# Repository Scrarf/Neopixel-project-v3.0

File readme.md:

# (work in progress) Status: Hardware verification. 

# Introduction:
A dimmable RGBW LED controller that can be controlled with wifi or bluetooth. A constant current DC-DC buck converter provides stable current to all leds connected in series, up to 3A. Currently, it is programmed for 300mah by R22 current sensing resistor for the apropriate onboard 300mah LEDs.

# 3D render:

# Schematic:

# Layout:

# Bill of materials:

|Reference               |Value               |Datasheet                                                                                           |Footprint                                                                         |Qty|PPU   |DNP|
|------------------------|--------------------|----------------------------------------------------------------------------------------------------|----------------------------------------------------------------------------------|---|------|---|
|C1,C2,C14               |100µF               |https://www.lcsc.com/datasheet/C22383783.pdf                                                        |Capacitor_SMD:CP_Elec_6.3x7.7                                                     |3  |0.0193|   |
|C3,C15,C16              |22µF                |https://www.lcsc.com/datasheet/C22367832.pdf                                                        |Capacitor_SMD:C_0805_2012Metric                                                   |3  |0.1158|   |
|C4                      |1µF                 |https://www.lcsc.com/datasheet/C15849.pdf                                                           |Capacitor_SMD:C_0603_1608Metric                                                   |1  |0.0038|   |
|C5                      |10nF                |https://www.lcsc.com/datasheet/C60133.pdf                                                           |Capacitor_SMD:C_0402_1005Metric                                                   |1  |0.0009|   |
|C6,C7,C9,C10,C11,C12,C13|100nF               |https://www.lcsc.com/datasheet/C14663.pdf                                                           |Capacitor_SMD:C_0603_1608Metric                                                   |7  |0.0021|   |
|C8                      |10µF                |https://www.lcsc.com/datasheet/C33546007.pdf                                                        |Capacitor_SMD:C_0805_2012Metric                                                   |1  |0.0178|   |
|C17,C18                 |24pF                |https://www.lcsc.com/datasheet/C541435.pdf                                                          |Capacitor_SMD:C_0402_1005Metric                                                   |2  |0.0033|   |
|C19,C20                 |DNP                 |~                                                                                                   |Capacitor_SMD:C_0402_1005Metric                                                   |2  |0     |DNP|
|D1                      |W                   |https://www.lcsc.com/datasheet/C7500126.pdf                                                         |LED_SMD:LED_PLCC_2835                                                             |1  |0.069 |   |
|D2                      |R                   |https://www.lcsc.com/datasheet/C1322327.pdf                                                         |LED_SMD:LED_Luminus_MP-3030-1100_3.0x3.0mm                                        |1  |0.1638|   |
|D3                      |G                   |https://www.lcsc.com/datasheet/C1322328.pdf                                                         |LED_SMD:LED_Luminus_MP-3030-1100_3.0x3.0mm                                        |1  |0.1589|   |
|D4                      |B                   |https://www.lcsc.com/datasheet/C1322329.pdf                                                         |LED_SMD:LED_Luminus_MP-3030-1100_3.0x3.0mm                                        |1  |0.0962|   |
|D5                      |SS34                |https://www.lcsc.com/datasheet/C8678.pdf                                                            |Diode_SMD:D_SMA                                                                   |1  |0.0265|   |
|HS1                     |Heatsink            |https://www.lcsc.com/datasheet/C286191.pdf                                                          |22x22x10                                                                          |1  |0.1324|   |
|J1                      |Conn_01x03_Pin      |https://www.lcsc.com/datasheet/C5383112.pdf                                                         |Connector_PinHeader_2.54mm:PinHeader_1x03_P2.54mm_Vertical                        |1  |0.0105|   |
|J3                      |Screw_Terminal_01x02|https://www.lcsc.com/datasheet/C5188442.pdf                                                         |TerminalBlock_Phoenix:TerminalBlock_Phoenix_MPT-0,5-2-2.54_1x02_P2.54mm_Horizontal|1  |0.1513|   |
|L1                      |68µH                |https://www.lcsc.com/datasheet/C2929435.pdf                                                         |Inductor_SMD:L_Ferrocore_DLG-0504                                                 |1  |0.052 |   |
|L2                      |2nH                 |https://www.lcsc.com/datasheet/C395081.pdf                                                          |Inductor_SMD:L_0603_1608Metric                                                    |1  |0.0069|   |
|L3                      |22µH                |https://www.lcsc.com/datasheet/C41408473.pdf                                                        |Inductor_SMD:L_Ferrocore_DLG-0302                                                 |1  |0.0184|   |
|L4                      |24nH                |https://www.lcsc.com/datasheet/C139271.pdf                                                          |Inductor_SMD:L_0603_1608Metric                                                    |1  |0.0064|   |
|L5                      |0                   |https://www.lcsc.com/datasheet/C106231.pdf                                                          |Inductor_SMD:L_0402_1005Metric                                                    |1  |0.0006|   |
|Q1,Q2,Q3,Q4             |MMBT3904            |https://www.lcsc.com/datasheet/C2762221.pdf                                                         |Package_TO_SOT_SMD:SOT-23                                                         |4  |0.0095|   |
|Q5,Q6,Q7,Q8             |DO3407B             |https://www.lcsc.com/datasheet/C41367402.pdf                                                        |Package_TO_SOT_SMD:SOT-23-3                                                       |4  |0.0271|   |
|R1,R3,R5,R7             |1k5                 |https://www.lcsc.com/datasheet/C2980089.pdf                                                         |Resistor_SMD:R_1206_3216Metric                                                    |4  |0.013 |   |
|R2,R4,R6,R8             |200                 |https://www.lcsc.com/datasheet/C3014166.pdf                                                         |Resistor_SMD:R_0805_2012Metric                                                    |4  |0.0156|   |
|R9,R10,R11,R12,R17      |5k1                 |https://www.lcsc.com/datasheet/C103696.pdf                                                          |Resistor_SMD:R_0603_1608Metric                                                    |5  |0.0009|   |
|R15                     |1M                  |https://www.lcsc.com/datasheet/C103216.pdf                                                          |Resistor_SMD:R_0603_1608Metric                                                    |1  |0.001 |   |
|R16                     |16k                 |https://www.lcsc.com/datasheet/C137788.pdf                                                          |Resistor_SMD:R_0603_1608Metric                                                    |1  |0.0012|   |
|R22                     |0.333               |https://www.lcsc.com/datasheet/C160932.pdf                                                          |Resistor_SMD:R_2512_6332Metric                                                    |1  |0.0488|   |
|SW1,SW2                 |TS-1088-AR02016     |https://www.lcsc.com/datasheet/C720477.pdf                                                          |TS-1088-AR02016:SW_TS-1088_XNP                                                    |2  |0.0415|   |
|U1                      |ESP8685H4           |https://www.lcsc.com/datasheet/C4944062.pdf                                                         |ESP8685:QFN284X4_EXP                                                              |1  |1.3435|   |
|U2                      |AL8843              |https://www.lcsc.com/datasheet/lcsc_datasheet_2412251103_Diodes-Incorporated-AL8843SP-13_C507866.pdf|Package_SO:Diodes_SO-8EP                                                          |1  |0.3568|   |
|U3                      |TD1469              |https://www.lcsc.com/datasheet/C2832208.pdf                                                         |Package_TO_SOT_SMD:TSOT-23-6                                                      |1  |0.2999|   |
|U4                      |USBLC6-4SC6         |https://www.lcsc.com/datasheet/C19170931.pdf                                                        |Package_TO_SOT_SMD:SOT-23-6                                                       |1  |0.0273|   |
|Y1                      |Crystal_GND24       |https://www.lcsc.com/datasheet/C501793.pdf                                                          |Crystal:Crystal_SMD_Abracon_ABM8AIG-4Pin_3.2x2.5mm                                |1  |0.0922|   |

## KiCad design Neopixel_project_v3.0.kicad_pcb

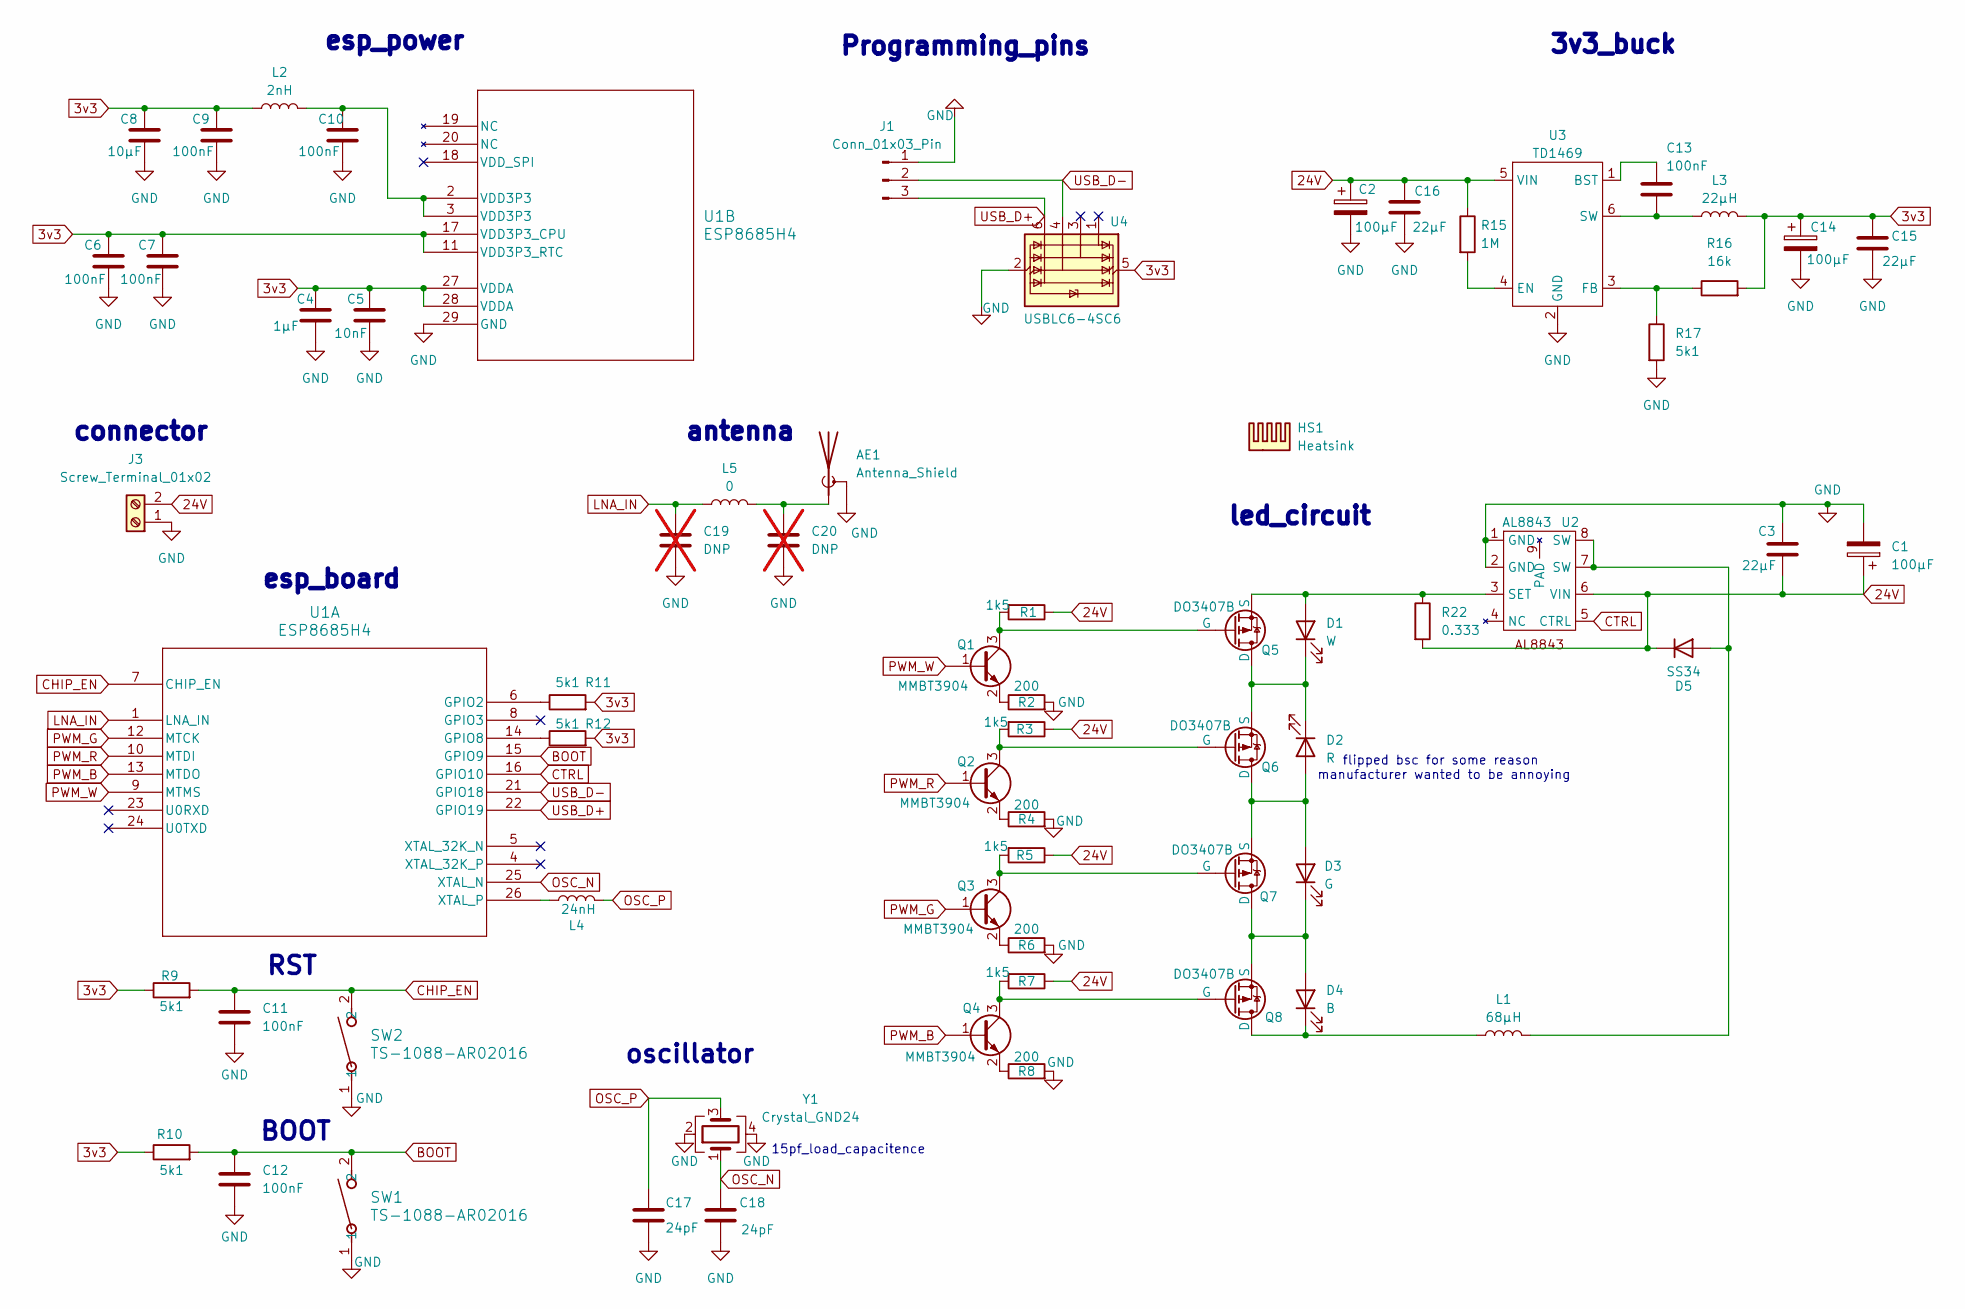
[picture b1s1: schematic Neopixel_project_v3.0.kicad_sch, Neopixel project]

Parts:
AE1: Antenna_Shield; Texas_SWRA117D_2.4GHz_Left
C1, C2, C14: 100µF; CP_Elec_6.3x7.7
C3, C15, C16: 22µF; C_0805_2012Metric
C4: 1µF; C_0603_1608Metric
C5: 10nF; C_0402_1005Metric
C6, C7, C9, C10, C11, C12, C13: 100nF; C_0603_1608Metric
C8: 10µF; C_0805_2012Metric
C17, C18: 24pF; C_0402_1005Metric
C19, C20: DNP; C_0402_1005Metric; not fitted
D1: W; LED_PLCC_2835
D2: R; LED_Luminus_MP-3030-1100_3.0x3.0mm
D3: G; LED_Luminus_MP-3030-1100_3.0x3.0mm
D4: B; LED_Luminus_MP-3030-1100_3.0x3.0mm
D5: SS34; D_SMA
HS1: Heatsink; 22x22x10
J1: Conn_01x03_Pin; PinHeader_1x03_P2.54mm_Vertical
J3: Screw_Terminal_01x02; TerminalBlock_Phoenix_MPT-0,5-2-2.54_1x02_P2.54mm_Horizontal
L1: 68µH; L_Ferrocore_DLG-0504
L2: 2nH; L_0603_1608Metric
L3: 22µH; L_Ferrocore_DLG-0302
L4: 24nH; L_0603_1608Metric
L5: 0; L_0402_1005Metric
Q1, Q2, Q3, Q4: MMBT3904; SOT-23
Q5, Q6, Q7, Q8: DO3407B; SOT-23-3
R1, R3, R5, R7: 1k5; R_1206_3216Metric
R2, R4, R6, R8: 200; R_0805_2012Metric
R9, R10, R11, R12, R17: 5k1; R_0603_1608Metric
R15: 1M; R_0603_1608Metric
R16: 16k; R_0603_1608Metric
R22: 0.333; R_2512_6332Metric
SW1, SW2: TS-1088-AR02016; SW_TS-1088_XNP
U1: ESP8685H4; QFN284X4_EXP
U2: AL8843; Diodes_SO-8EP
U3: TD1469; TSOT-23-6
U4: USBLC6-4SC6; SOT-23-6
Y1: Crystal_GND24; Crystal_SMD_Abracon_ABM8AIG-4Pin_3.2x2.5mm

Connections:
3v3: C4.1, C5.1, C6.1, C7.1, C8.1, C9.1, C14.1, C15.1, L2.1, L3.2, R9.1, R10.1, R11.2, R12.2, R16.2, U1.11 (VDD3P3_RTC), U1.17 (VDD3P3_CPU), U1.27 (VDDA), U1.28 (VDDA), U4.5 (VBUS)
24V: C1.1, C2.1, C3.2, C16.1, D5.1 (K), J3.2, R1.1, R3.1, R5.1, R7.1, R15.1, R22.2, U2.6 (VIN), U3.5 (VIN)
BOOT: C12.1, R10.2, SW1.2, U1.15 (GPIO9)
CHIP_EN: C11.1, R9.2, SW2.2, U1.7 (CHIP_EN)
CTRL: U1.16 (GPIO10), U2.5 (CTRL)
GND: AE1.2 (Shield), C1.2, C2.2, C3.1, C4.2, C5.2, C6.2, C7.2, C8.2, C9.2, C10.2, C11.2, C12.2, C14.2, C15.2, C16.2, C17.2, C18.2, C19.2, C20.2, J1.1, J3.1, R2.2, R4.2, R6.2, R8.2, R17.2, SW1.1, SW2.1, U1.29 (GND), U2.1 (GND), U2.2 (GND), U3.2 (GND), U4.2 (GND), Y1.2, Y1.4
LNA_IN: C19.1, L5.1, U1.1 (LNA_IN)
unnamed: AE1.1 (A), C20.1, L5.2
unnamed: C10.1, L2.2, U1.2 (VDD3P3), U1.3 (VDD3P3)
unnamed: D1.2 (A), Q5.3 (S), R22.1, U2.3 (SET)
unnamed: D1.1 (K), D2.1 (K), Q5.1 (D), Q6.3 (S)
unnamed: D2.2 (A), D3.2 (A), Q6.1 (D), Q7.3 (S)
unnamed: D3.1 (K), D4.2 (A), Q7.1 (D), Q8.3 (S)
unnamed: D4.1 (K), L1.1, Q8.1 (D)
unnamed: D5.2 (A), L1.2, U2.7 (SW), U2.8 (SW)
unnamed: Q1.3 (C), Q5.2 (G), R1.2
unnamed: Q1.2 (E), R2.1
unnamed: Q2.3 (C), Q6.2 (G), R3.2
unnamed: Q2.2 (E), R4.1
unnamed: Q3.3 (C), Q7.2 (G), R5.2
unnamed: Q3.2 (E), R6.1
unnamed: Q4.3 (C), Q8.2 (G), R7.2
unnamed: Q4.2 (E), R8.1
unnamed: R11.1, U1.6 (GPIO2)
unnamed: R12.1, U1.14 (GPIO8)
unnamed: L4.1, U1.26 (XTAL_P)
unnamed: C13.1, U3.1 (BST)
unnamed: R15.2, U3.4 (EN)
unnamed: R16.1, R17.1, U3.3 (FB)
unnamed: C13.2, L3.1, U3.6 (SW)
OSC_N: C18.1, U1.25 (XTAL_N), Y1.1
OSC_P: C17.1, L4.2, Y1.3
PWM_B: Q4.1 (B), U1.13 (MTDO)
PWM_G: Q3.1 (B), U1.12 (MTCK)
PWM_R: Q2.1 (B), U1.10 (MTDI)
PWM_W: Q1.1 (B), U1.9 (MTMS)
USB_D+: J1.3, U1.22 (GPIO19), U4.6 (I/O4)
USB_D-: J1.2, U1.21 (GPIO18), U4.4 (I/O3)

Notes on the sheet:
RST
esp_power
led_circuit
flipped bsc for some reason manufacturer wanted to be annoying
connector
3v3_buck
antenna
Programming_pins
15pf_load_capacitence
oscillator
BOOT
esp_board

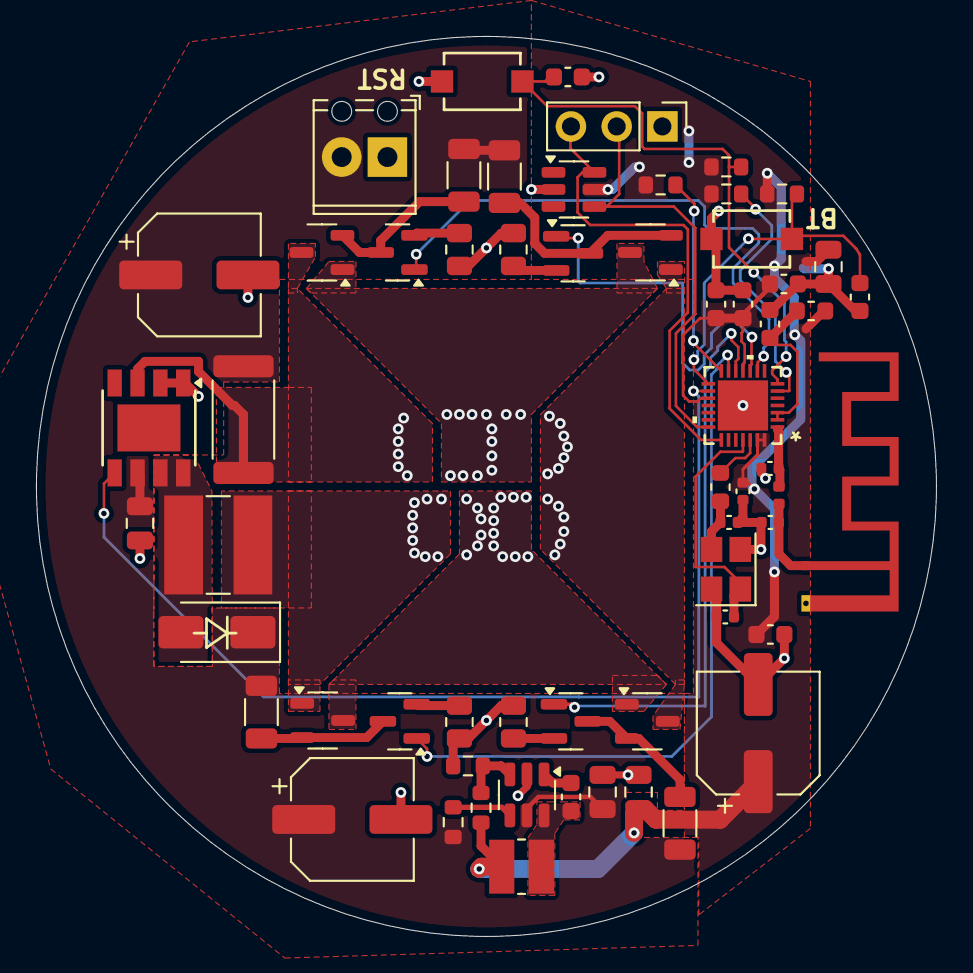
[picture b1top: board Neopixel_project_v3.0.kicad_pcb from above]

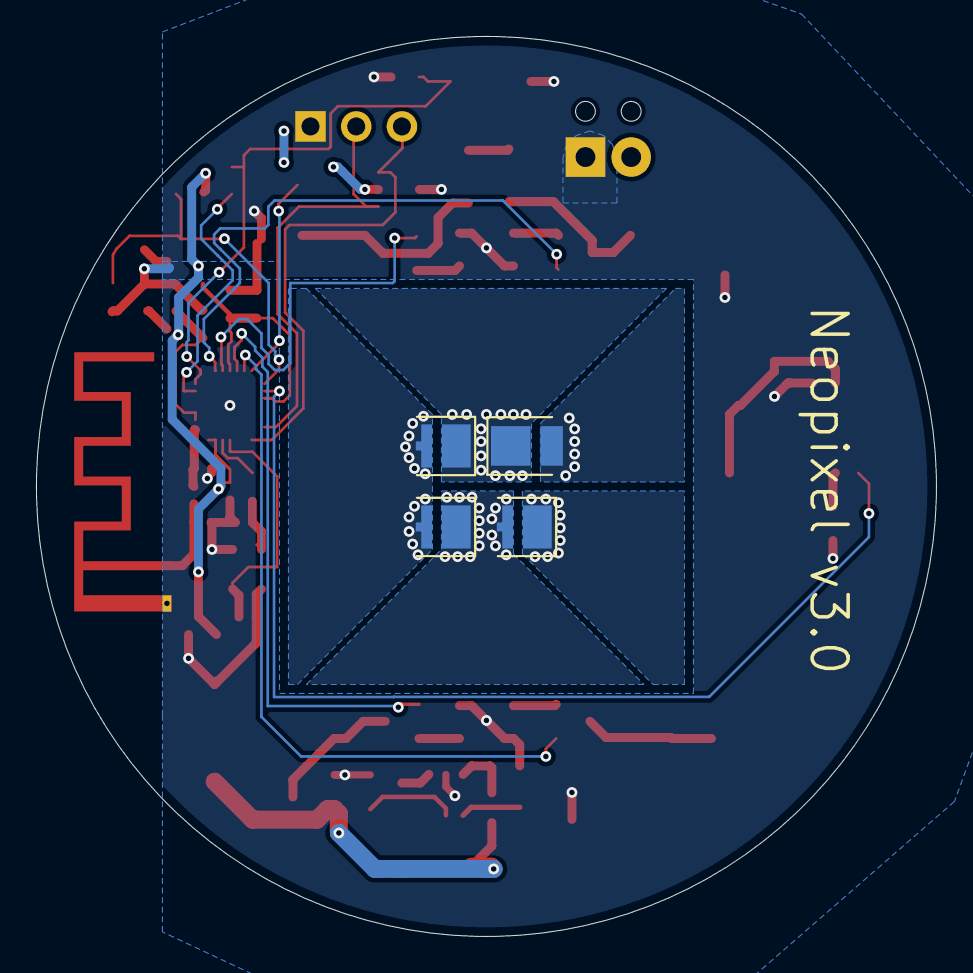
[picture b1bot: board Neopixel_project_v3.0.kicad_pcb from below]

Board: 2 copper layers, 50.0 x 50.0 mm, 64 parts (4 on the bottom side), 38 nets.

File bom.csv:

"Reference","Value","Datasheet","Footprint","Qty","PPU","DNP"
"C1,C2,C14","100µF","https://www.lcsc.com/datasheet/C22383783.pdf","Capacitor_SMD:CP_Elec_6.3x7.7","3","0.0193",""
"C3,C15,C16","22µF","https://www.lcsc.com/datasheet/C22367832.pdf","Capacitor_SMD:C_0805_2012Metric","3","0.1158",""
"C4","1µF","https://www.lcsc.com/datasheet/C15849.pdf","Capacitor_SMD:C_0603_1608Metric","1","0.0038",""
"C5","10nF","https://www.lcsc.com/datasheet/C60133.pdf","Capacitor_SMD:C_0402_1005Metric","1","0.0009",""
"C6,C7,C9,C10,C11,C12,C13","100nF","https://www.lcsc.com/datasheet/C14663.pdf","Capacitor_SMD:C_0603_1608Metric","7","0.0021",""
"C8","10µF","https://www.lcsc.com/datasheet/C33546007.pdf","Capacitor_SMD:C_0805_2012Metric","1","0.0178",""
"C17,C18","24pF","https://www.lcsc.com/datasheet/C541435.pdf","Capacitor_SMD:C_0402_1005Metric","2","0.0033",""
"C19,C20","DNP","~","Capacitor_SMD:C_0402_1005Metric","2","0","DNP"
"D1","W","https://www.lcsc.com/datasheet/C7500126.pdf","LED_SMD:LED_PLCC_2835","1","0.069",""
"D2","R","https://www.lcsc.com/datasheet/C1322327.pdf","LED_SMD:LED_Luminus_MP-3030-1100_3.0x3.0mm","1","0.1638",""
"D3","G","https://www.lcsc.com/datasheet/C1322328.pdf","LED_SMD:LED_Luminus_MP-3030-1100_3.0x3.0mm","1","0.1589",""
"D4","B","https://www.lcsc.com/datasheet/C1322329.pdf","LED_SMD:LED_Luminus_MP-3030-1100_3.0x3.0mm","1","0.0962",""
"D5","SS34","https://www.lcsc.com/datasheet/C8678.pdf","Diode_SMD:D_SMA","1","0.0265",""
"HS1","Heatsink","https://www.lcsc.com/datasheet/C286191.pdf","22x22x10","1","0.1324",""
"J1","Conn_01x03_Pin","https://www.lcsc.com/datasheet/C5383112.pdf","Connector_PinHeader_2.54mm:PinHeader_1x03_P2.54mm_Vertical","1","0.0105",""
"J3","Screw_Terminal_01x02","https://www.lcsc.com/datasheet/C5188442.pdf","TerminalBlock_Phoenix:TerminalBlock_Phoenix_MPT-0,5-2-2.54_1x02_P2.54mm_Horizontal","1","0.1513",""
"L1","68µH","https://www.lcsc.com/datasheet/C2929435.pdf","Inductor_SMD:L_Ferrocore_DLG-0504","1","0.052",""
"L2","2nH","https://www.lcsc.com/datasheet/C395081.pdf","Inductor_SMD:L_0603_1608Metric","1","0.0069",""
"L3","22µH","https://www.lcsc.com/datasheet/C41408473.pdf","Inductor_SMD:L_Ferrocore_DLG-0302","1","0.0184",""
"L4","24nH","https://www.lcsc.com/datasheet/C139271.pdf","Inductor_SMD:L_0603_1608Metric","1","0.0064",""
"L5","0","https://www.lcsc.com/datasheet/C106231.pdf","Inductor_SMD:L_0402_1005Metric","1","0.0006",""
"Q1,Q2,Q3,Q4","MMBT3904","https://www.lcsc.com/datasheet/C2762221.pdf","Package_TO_SOT_SMD:SOT-23","4","0.0095",""
"Q5,Q6,Q7,Q8","DO3407B","https://www.lcsc.com/datasheet/C41367402.pdf","Package_TO_SOT_SMD:SOT-23-3","4","0.0271",""
"R1,R3,R5,R7","1k5","https://www.lcsc.com/datasheet/C2980089.pdf","Resistor_SMD:R_1206_3216Metric","4","0.013",""
"R2,R4,R6,R8","200","https://www.lcsc.com/datasheet/C3014166.pdf","Resistor_SMD:R_0805_2012Metric","4","0.0156",""
"R9,R10,R11,R12,R17","5k1","https://www.lcsc.com/datasheet/C103696.pdf","Resistor_SMD:R_0603_1608Metric","5","0.0009",""
"R15","1M","https://www.lcsc.com/datasheet/C103216.pdf","Resistor_SMD:R_0603_1608Metric","1","0.001",""
"R16","16k","https://www.lcsc.com/datasheet/C137788.pdf","Resistor_SMD:R_0603_1608Metric","1","0.0012",""
"R22","0.333","https://www.lcsc.com/datasheet/C160932.pdf","Resistor_SMD:R_2512_6332Metric","1","0.0488",""
"SW1,SW2","TS-1088-AR02016","https://www.lcsc.com/datasheet/C720477.pdf","TS-1088-AR02016:SW_TS-1088_XNP","2","0.0415",""
"U1","ESP8685H4","https://www.lcsc.com/datasheet/C4944062.pdf","ESP8685:QFN284X4_EXP","1","1.3435",""
"U2","AL8843","https://www.lcsc.com/datasheet/lcsc_datasheet_2412251103_Dio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","Package_SO:Diodes_SO-8EP","1","0.3568",""
"U3","TD1469","https://www.lcsc.com/datasheet/C2832208.pdf","Package_TO_SOT_SMD:TSOT-23-6","1","0.2999",""
"U4","USBLC6-4SC6","https://www.lcsc.com/datasheet/C19170931.pdf","Package_TO_SOT_SMD:SOT-23-6","1","0.0273",""
"Y1","Crystal_GND24","https://www.lcsc.com/datasheet/C501793.pdf","Crystal:Crystal_SMD_Abracon_ABM8AIG-4Pin_3.2x2.5mm","1","0.0922",""

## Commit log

2025-09-07 inception
2025-09-07 rename
2025-09-07 gitignore blacklist useless stuff
2025-09-07 removed unesesarry files
2025-09-07 remove bom.csv
2025-09-09 snapshot save
2025-09-09 pcb finished
2025-09-09 pcb and 3d models finished
2025-09-09 added bom.csv and buch of other changes
2025-09-09 excluded autosave
2025-09-09 added heatsink to bom
2025-09-09 docs
2025-09-10 added readme
2025-09-10 update name
2025-09-10 silkscreen removed and layout printed
2025-09-10 added layout.png
2025-09-10 added status
2025-09-10 added gerber files
2025-09-11 bom viewer
2025-09-12 updated gerber
2025-09-12 updated render and silkscreen
